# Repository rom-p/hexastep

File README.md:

6-axis stepper driver for **Raspberry Pi Pico**

The **Raspberry Pi Pico** is on the back side of this board

# Prerequisites
* KiCad 6.0+
* load symbols and footprints.  The schematic and PCB depend on the library located in `/libs`, which needs to be added before opening the schematics/pcb in KiCad:
  * symbols: **KiCad** -> **Preferences** -> **Manage Symbol Libraries...**,
  * footprints: **KiCad** -> **Preferences** -> **Manage Footprint Libraries...**
* PCB manufacturing: any manufacturer capable of 4-layer and 0.4mm vias -- pretty much any PCB shop

# Schematic
  (also in [PDF](docs/schematic-v1.pdf))

# Parts
https://octopart.com/bom-tool/PoB5E81H

# Footnotes
the photo at the top of this page is of a previous version of the board.  The current version has:
  * a slightly different layout
  * a power LED
  * a jumper for powering R-Pi Pico
  * better filtering.

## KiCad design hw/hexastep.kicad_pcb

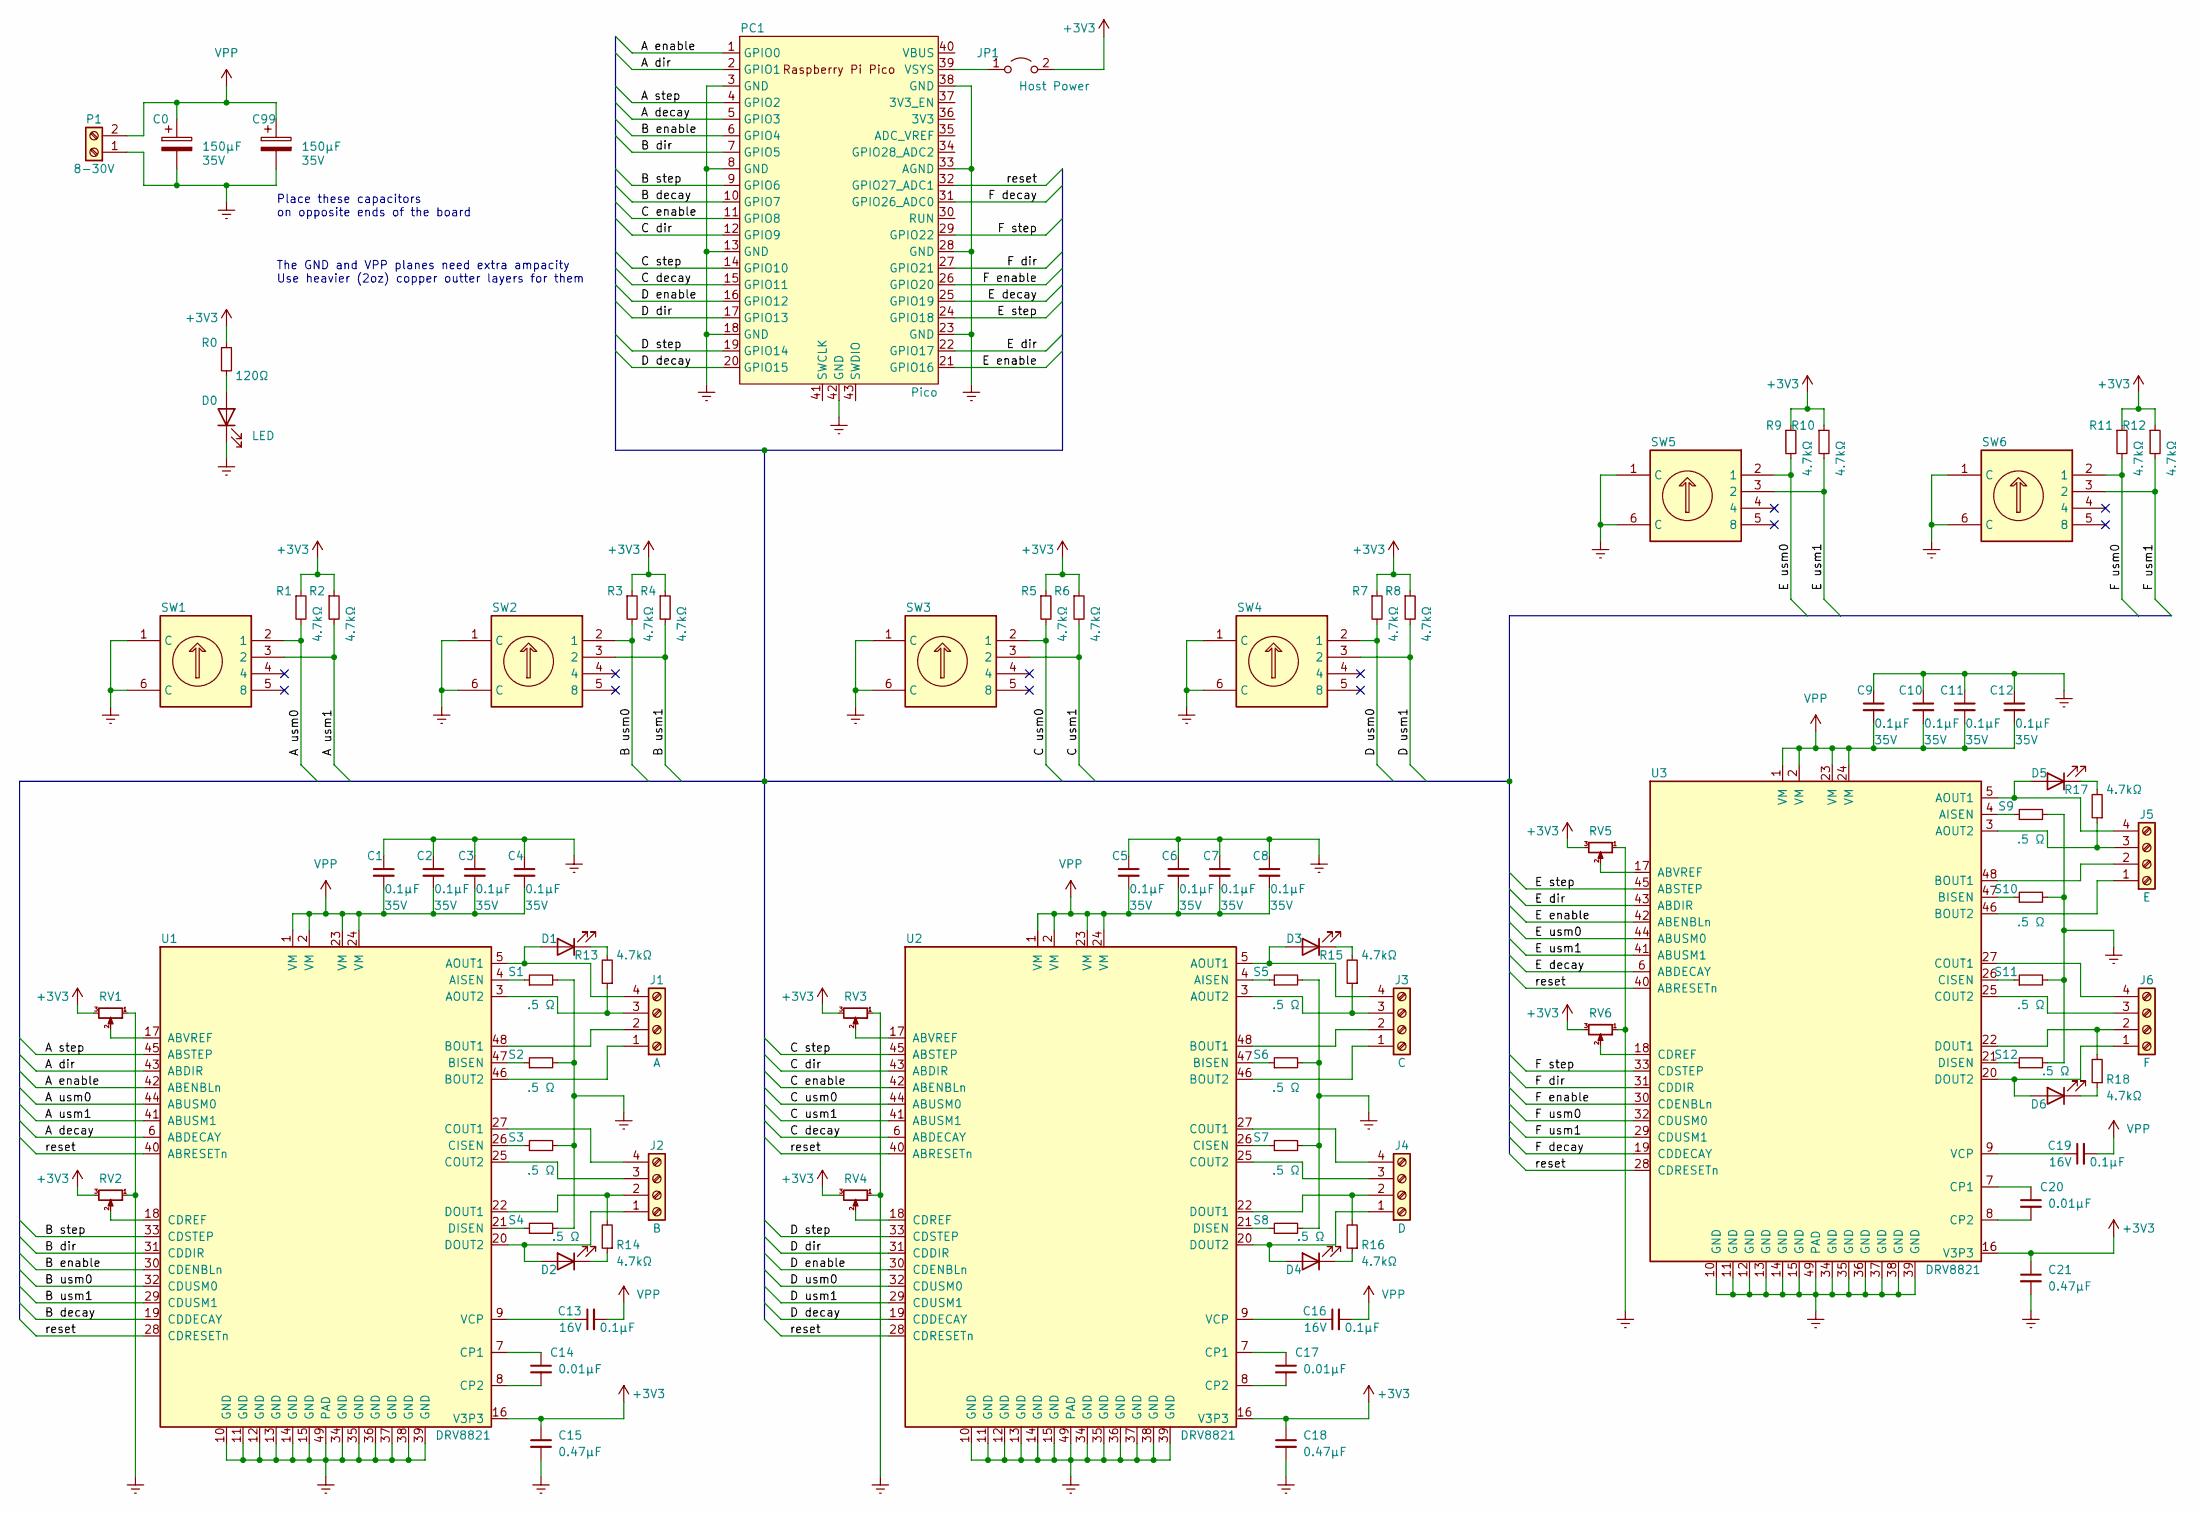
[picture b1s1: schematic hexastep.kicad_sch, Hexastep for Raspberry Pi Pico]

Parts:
C0, C99: 150µF; CP_Elec_8x10; Voltage 35V
C1, C2, C3, C4, C5, C6, C7, C8, C9, C10, C11, C12: 0.1µF; C_0402_1005Metric_Pad0.74x0.62mm_HandSolder; Voltage 35V
C13, C16, C19: 0.1µF; C_0402_1005Metric_Pad0.74x0.62mm_HandSolder; Voltage 16V
C14, C17, C20: 0.01µF; C_0402_1005Metric_Pad0.74x0.62mm_HandSolder
C15, C18, C21: 0.47µF; C_0402_1005Metric_Pad0.74x0.62mm_HandSolder
D0, D1, D2, D3, D4, D5, D6: LED; LED_0603_1608Metric_Pad1.05x0.95mm_HandSolder
J1: A; TerminalBlock_Phoenix_PT-1,5-4-3.5-H_1x04_P3.50mm_Horizontal
J2: B; TerminalBlock_Phoenix_PT-1,5-4-3.5-H_1x04_P3.50mm_Horizontal
J3: C; TerminalBlock_Phoenix_PT-1,5-4-3.5-H_1x04_P3.50mm_Horizontal
J4: D; TerminalBlock_Phoenix_PT-1,5-4-3.5-H_1x04_P3.50mm_Horizontal
J5: E; TerminalBlock_Phoenix_PT-1,5-4-3.5-H_1x04_P3.50mm_Horizontal
J6: F; TerminalBlock_Phoenix_PT-1,5-4-3.5-H_1x04_P3.50mm_Horizontal
JP1: Host Power; TestPoint_2Pads_Pitch5.08mm_Drill1.3mm
P1: 8-30V; TerminalBlock_Phoenix_MKDS-1,5-2-5.08_1x02_P5.08mm_Horizont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
PC1: Pico; RPi_Pico_SMD_only
R0: 120Ω; R_0402_1005Metric_Pad0.72x0.64mm_HandSolder
R1, R2, R3, R4, R5, R6, R7, R8, R9, R10, R11, R12, R13, R14, R15, R16, R17, R18: 4.7kΩ; R_0402_1005Metric_Pad0.72x0.64mm_HandSolder
RV1, RV2, RV3, RV4, RV5, RV6: R_Potentiometer_Small; Potentiometer_ACP_CA6-VSMD_Vertical
S1, S2, S3, S4, S5, S6, S7, S8, S9, S10, S11, S12: .5 Ω; R_1206_3216Metric_Pad1.30x1.75mm_HandSolder
SW1, SW2, SW3, SW4, SW5, SW6: (no value)
U1, U2, U3: DRV8821; HTSSOP-48_6.1x12.5mm_P0.5mm

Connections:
+3V3: C15.1, C18.1, C21.1, JP1.2 (B), R0.1, R1.1, R2.1, R3.1, R4.1, R5.1, R6.1, R7.1, R8.1, R9.1, R10.1, R11.1, R12.1, RV1.3, RV2.3, RV3.3, RV4.3, RV5.3, RV6.3, U1.16 (V3P3), U2.16 (V3P3), U3.16 (V3P3)
/A decay: PC1.5 (GPIO3), U1.6 (ABDECAY)
/A dir: PC1.2 (GPIO1), U1.43 (ABDIR)
/A enable: PC1.1 (GPIO0), U1.42 (ABENBLn)
/A step: PC1.4 (GPIO2), U1.45 (ABSTEP)
/A usm0: R1.2, SW1.2 (1), U1.44 (ABUSM0)
/A usm1: R2.2, SW1.3 (2), U1.41 (ABUSM1)
/B decay: PC1.10 (GPIO7), U1.19 (CDDECAY)
/B dir: PC1.7 (GPIO5), U1.31 (CDDIR)
/B enable: PC1.6 (GPIO4), U1.30 (CDENBLn)
/B step: PC1.9 (GPIO6), U1.33 (CDSTEP)
/B usm0: R3.2, SW2.2 (1), U1.32 (CDUSM0)
/B usm1: R4.2, SW2.3 (2), U1.29 (CDUSM1)
/C decay: PC1.15 (GPIO11), U2.6 (ABDECAY)
/C dir: PC1.12 (GPIO9), U2.43 (ABDIR)
/C enable: PC1.11 (GPIO8), U2.42 (ABENBLn)
/C step: PC1.14 (GPIO10), U2.45 (ABSTEP)
/C usm0: R5.2, SW3.2 (1), U2.44 (ABUSM0)
/C usm1: R6.2, SW3.3 (2), U2.41 (ABUSM1)
/D decay: PC1.20 (GPIO15), U2.19 (CDDECAY)
/D dir: PC1.17 (GPIO13), U2.31 (CDDIR)
/D enable: PC1.16 (GPIO12), U2.30 (CDENBLn)
/D step: PC1.19 (GPIO14), U2.33 (CDSTEP)
/D usm0: R7.2, SW4.2 (1), U2.32 (CDUSM0)
/D usm1: R8.2, SW4.3 (2), U2.29 (CDUSM1)
/E decay: PC1.25 (GPIO19), U3.6 (ABDECAY)
/E dir: PC1.22 (GPIO17), U3.43 (ABDIR)
/E enable: PC1.21 (GPIO16), U3.42 (ABENBLn)
/E step: PC1.24 (GPIO18), U3.45 (ABSTEP)
/E usm0: R9.2, SW5.2 (1), U3.44 (ABUSM0)
/E usm1: R10.2, SW5.3 (2), U3.41 (ABUSM1)
/F decay: PC1.31 (GPIO26_ADC0), U3.19 (CDDECAY)
/F dir: PC1.27 (GPIO21), U3.31 (CDDIR)
/F enable: PC1.26 (GPIO20), U3.30 (CDENBLn)
/F step: PC1.29 (GPIO22), U3.33 (CDSTEP)
/F usm0: R11.2, SW6.2 (1), U3.32 (CDUSM0)
/F usm1: R12.2, SW6.3 (2), U3.29 (CDUSM1)
/reset: PC1.32 (GPIO27_ADC1), U1.28 (CDRESETn), U1.40 (ABRESETn), U2.28 (CDRESETn), U2.40 (ABRESETn), U3.28 (CDRESETn), U3.40 (ABRESETn)
Earth: C0.2, C1.1, C2.1, C3.1, C4.1, C5.1, C6.1, C7.1, C8.1, C9.1, C10.1, C11.1, C12.1, C15.2, C18.2, C21.2, C99.2, D0.1 (K), P1.1, PC1.3 (GND), PC1.8 (GND), PC1.13 (GND), PC1.18 (GND), PC1.23 (GND), PC1.28 (GND), PC1.33 (AGND), PC1.38 (GND), PC1.42 (GND), RV1.1, RV2.1, RV3.1, RV4.1, RV5.1, RV6.1, S1.2, S2.2, S3.2, S4.2, S5.2, S6.2, S7.2, S8.2, S9.2, S10.2, S11.2, S12.2, SW1.1 (C), SW1.6 (C), SW2.1 (C), SW2.6 (C), SW3.1 (C), SW3.6 (C), SW4.1 (C), SW4.6 (C), SW5.1 (C), SW5.6 (C), SW6.1 (C), SW6.6 (C), U1.10 (GND), U1.11 (GND), U1.12 (GND), U1.13 (GND), U1.14 (GND), U1.15 (GND), U1.34 (GND), U1.35 (GND), U1.36 (GND), U1.37 (GND), U1.38 (GND), U1.39 (GND), U1.49 (PAD), U2.10 (GND), U2.11 (GND), U2.12 (GND), U2.13 (GND), U2.14 (GND), U2.15 (GND), U2.34 (GND), U2.35 (GND), U2.36 (GND), U2.37 (GND), U2.38 (GND), U2.39 (GND), U2.49 (PAD), U3.10 (GND), U3.11 (GND), U3.12 (GND), U3.13 (GND), U3.14 (GND), U3.15 (GND), U3.34 (GND), U3.35 (GND), U3.36 (GND), U3.37 (GND), U3.38 (GND), U3.39 (GND), U3.49 (PAD); also elsewhere on the board
unnamed: C13.1, U1.9 (VCP)
unnamed: C14.1, U1.7 (CP1)
unnamed: C14.2, U1.8 (CP2)
unnamed: C16.1, U2.9 (VCP)
unnamed: C17.1, U2.7 (CP1)
unnamed: C17.2, U2.8 (CP2)
unnamed: C19.1, U3.9 (VCP)
unnamed: C20.1, U3.7 (CP1)
unnamed: C20.2, U3.8 (CP2)
unnamed: D0.2 (A), R0.2
unnamed: D1.1 (K), R13.2
unnamed: D1.2 (A), J1.4, U1.5 (AOUT1)
unnamed: D2.1 (K), R14.1
unnamed: D2.2 (A), J2.1, U1.20 (DOUT2)
unnamed: D3.1 (K), R15.2
unnamed: D3.2 (A), J3.4, U2.5 (AOUT1)
unnamed: D4.1 (K), R16.1
unnamed: D4.2 (A), J4.1, U2.20 (DOUT2)
unnamed: D5.1 (K), R17.2
unnamed: D5.2 (A), J5.4, U3.5 (AOUT1)
unnamed: D6.1 (K), R18.1
unnamed: D6.2 (A), J6.1, U3.20 (DOUT2)
unnamed: J1.1, U1.46 (BOUT2)
unnamed: J1.2, U1.48 (BOUT1)
unnamed: J1.3, R13.1, U1.3 (AOUT2)
unnamed: J2.2, R14.2, U1.22 (DOUT1)
unnamed: J2.3, U1.25 (COUT2)
unnamed: J2.4, U1.27 (COUT1)
unnamed: J3.2, U2.48 (BOUT1)
unnamed: J3.3, R15.1, U2.3 (AOUT2)
unnamed: J4.2, R16.2, U2.22 (DOUT1)
unnamed: J4.3, U2.25 (COUT2)
unnamed: J4.4, U2.27 (COUT1)
unnamed: J5.2, U3.48 (BOUT1)
unnamed: J5.3, R17.1, U3.3 (AOUT2)
unnamed: J6.2, R18.2, U3.22 (DOUT1)
unnamed: J6.3, U3.25 (COUT2)
unnamed: J6.4, U3.27 (COUT1)
unnamed: JP1.1 (A), PC1.39 (VSYS)
unnamed: RV1.2, U1.17 (ABVREF)
unnamed: RV2.2, U1.18 (CDREF)
unnamed: RV3.2, U2.17 (ABVREF)
unnamed: RV4.2, U2.18 (CDREF)
unnamed: RV5.2, U3.17 (ABVREF)
unnamed: RV6.2, U3.18 (CDREF)
unnamed: S1.1, U1.4 (AISEN)
unnamed: S2.1, U1.47 (BISEN)
unnamed: S3.1, U1.26 (CISEN)
unnamed: S4.1, U1.21 (DISEN)
unnamed: S5.1, U2.4 (AISEN)
unnamed: S6.1, U2.47 (BISEN)
unnamed: S7.1, U2.26 (CISEN)
unnamed: S8.1, U2.21 (DISEN)
unnamed: S9.1, U3.4 (AISEN)
unnamed 93: S10.1, U3.47 (BISEN); also elsewhere on the board
unnamed 94: S11.1, U3.26 (CISEN); also elsewhere on the board
unnamed 95: S12.1, U3.21 (DISEN); also elsewhere on the board
unnamed: J3.1, U2.46 (BOUT2)
unnamed: J5.1, U3.46 (BOUT2)
VPP: C0.1, C1.2, C2.2, C3.2, C4.2, C5.2, C6.2, C7.2, C8.2, C9.2, C10.2, C11.2, C12.2, C13.2, C16.2, C19.2, C99.1, P1.2, U1.1 (VM), U1.2 (VM), U1.23 (VM), U1.24 (VM), U2.1 (VM), U2.2 (VM), U2.23 (VM), U2.24 (VM), U3.1 (VM), U3.2 (VM), U3.23 (VM), U3.24 (VM)

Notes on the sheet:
Place these capacitors on opposite ends of the board
The GND and VPP planes need extra ampacity Use heavier (2oz) copper outter layers for them

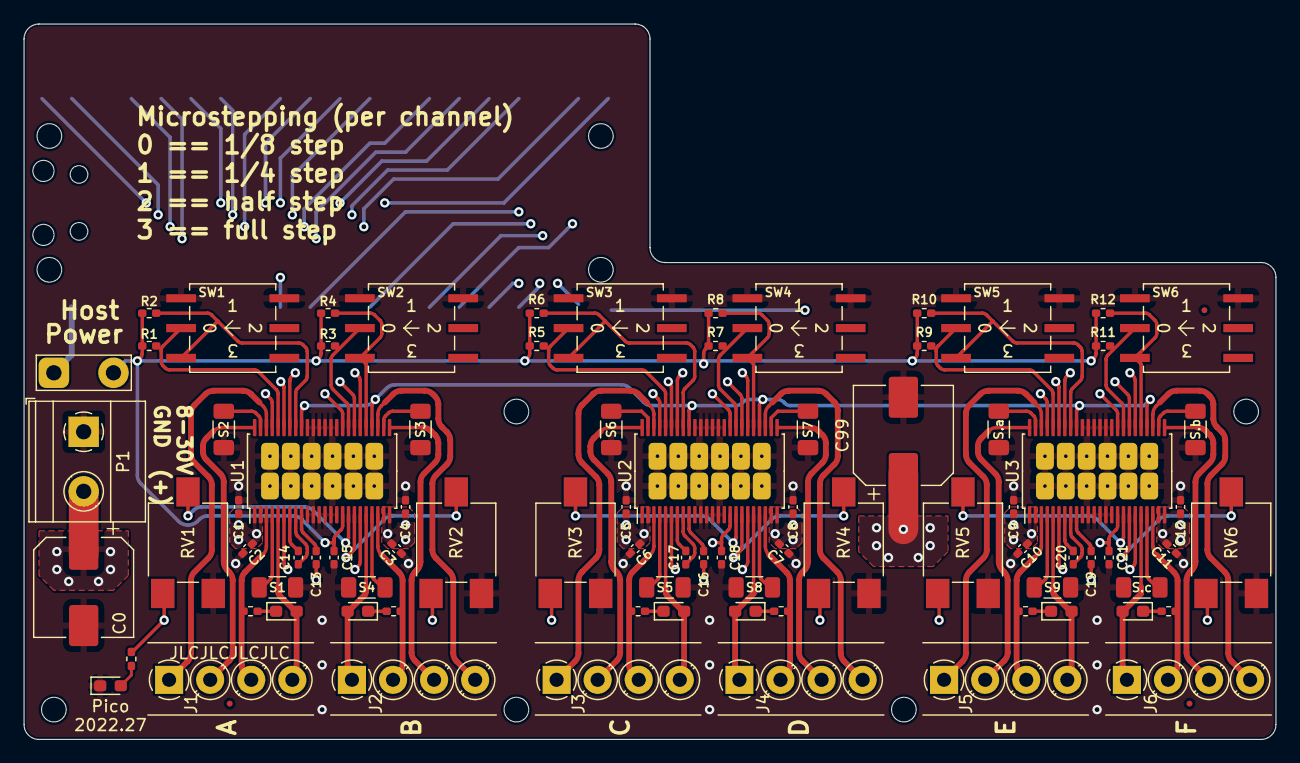
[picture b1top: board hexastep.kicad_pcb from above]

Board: 4 copper layers, 106.7 x 61.0 mm, 85 parts (1 on the bottom side), 99 nets.

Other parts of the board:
S.a, S.b, S.c: .5 Ω; R_1206_3216Metric_Pad1.30x1.75mm_HandSolder

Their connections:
Earth: S.a.2, S.b.2, S.c.2; also elsewhere on the board
unnamed 93: S.a.1; also elsewhere on the board
unnamed 94: S.b.1; also elsewhere on the board
unnamed 95: S.c.1; also elsewhere on the board

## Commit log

2022-07-14 original version, brought up 2022.06. SW to follow
